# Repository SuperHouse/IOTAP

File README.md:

IoT WiFi Access Point
=====================

Simple WiFi devices typically don't support enterprise level WiFi
authentication, which means they all share a single password. If
an IoT device is compromised, the password can be exposed and changing
the password on many devices is painful.

This project aims to create a WiFi access point that supports
personal pre-shared keys (PPSK) so that each device can be given its
own password. Access privileges for any device can then be revoked
without requiring changes to any other device.

More information is available at:

  https://www.superhouse.tv/iotap

Hardware
--------
The "Hardware" directory contains the PCB design as an EAGLE project.

Enclosure
---------
The enclosure is model AK-NW-40 from SZOMK:

  https://www.aliexpress.com/item/33043522751.html

Credits
-------
 * Jonathan Oxer <jon@oxer.com.au>
 * Tony Smith
 * Austin's Creations <https://www.austinscreations.ca/>
 * All the folks watching and commenting on the streams!

License
-------
Copyright 2020-2022 SuperHouse Automation Pty Ltd  www.superhouse.tv  

The hardware portion of this project is licensed under the TAPR Open
Hardware License (www.tapr.org/OHL). The "license" folder within this
repository contains a copy of this license in plain text format.

The software portion of this project is licensed under the Simplified
BSD License. The "licence" folder within this project contains a
copy of this license in plain text format.

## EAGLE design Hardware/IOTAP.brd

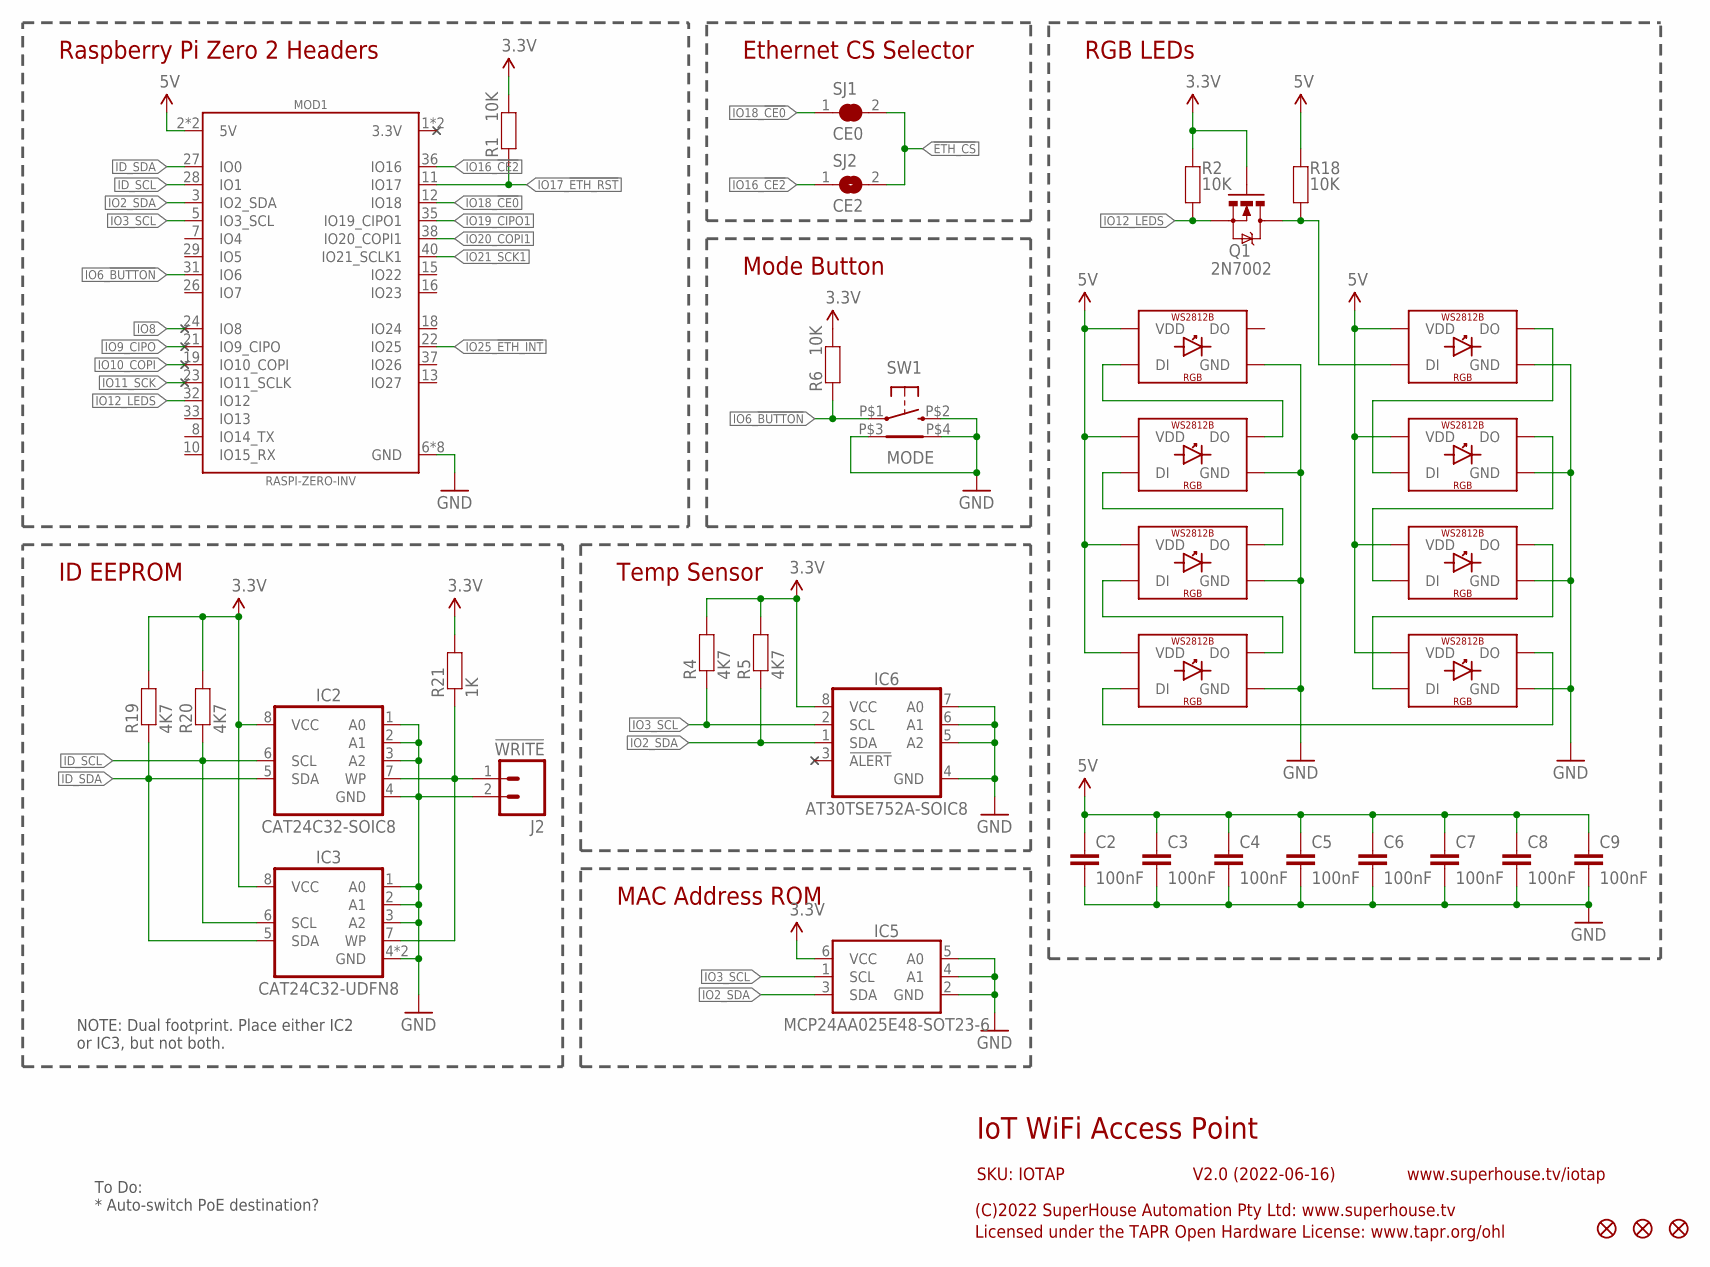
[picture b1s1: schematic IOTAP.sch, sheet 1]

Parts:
C2, C3, C4, C5, C6, C7, C8, C9: 100nF; C0603
FID1, FID2, FID3: FIDUCIAL1X2.5; FIDUCIAL-1X2.5
IC2: CAT24C32-SOIC8; SOIC8
IC3: CAT24C32-UDFN8; UDFN8
IC5: MCP24AA025E48-SOT23-6; SOT23-6
IC6: AT30TSE752A-SOIC8; SOIC8
J2: !WRITE; 1X02
LED1, LED2, LED3, LED4, LED5, LED6, LED7, LED8: WS2812B5050; WS2812B
MOD1: RASPI-ZERO-INV; RPI-ZERO-INV
Q1: 2N7002; SOT23-3
R1, R2, R6, R18: 10K; R0603
R4, R5, R19, R20: 4K7; R0603
R21: 1K; R0603
SJ1: CE0; SJC
SJ2: CE2; SJ
SW1: MODE; TC-120V

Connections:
3.3V: IC2.8 (VCC), IC3.8 (VCC), IC5.6 (VCC), IC6.8 (VCC), Q1.1 (G), R1.2, R2.2, R4.2, R5.2, R6.2, R19.2, R20.2, R21.2; also elsewhere on the board
5V: C2.1, C3.1, C4.1, C5.1, C6.1, C7.1, C8.1, C9.1, LED1.1-VDD (VDD), LED2.1-VDD (VDD), LED3.1-VDD (VDD), LED4.1-VDD (VDD), LED5.1-VDD (VDD), LED6.1-VDD (VDD), LED7.1-VDD (VDD), LED8.1-VDD (VDD), MOD1.2 (5V), MOD1.4 (5V), R18.2; also elsewhere on the board
!ETH_CS: SJ1.2, SJ2.2; also elsewhere on the board
GND: C2.2, C3.2, C4.2, C5.2, C6.2, C7.2, C8.2, C9.2, IC2.1 (A0), IC2.2 (A1), IC2.3 (A2), IC2.4 (GND), IC3.1 (A0), IC3.2 (A1), IC3.3 (A2), IC3.4 (GND), IC3.PAD (GND), IC5.2 (GND), IC5.4 (A1), IC5.5 (A0), IC6.4 (GND), IC6.5 (A2), IC6.6 (A1), IC6.7 (A0), J2.2, LED1.3-GND (GND), LED2.3-GND (GND), LED3.3-GND (GND), LED4.3-GND (GND), LED5.3-GND (GND), LED6.3-GND (GND), LED7.3-GND (GND), LED8.3-GND (GND), MOD1.6 (GND), MOD1.9 (GND), MOD1.14 (GND), MOD1.20 (GND), MOD1.25 (GND), MOD1.30 (GND), MOD1.34 (GND), MOD1.39 (GND), SW1.P$2 (2), SW1.P$3 (TAB1), SW1.P$4 (TAB2); also elsewhere on the board
ID_SCL: IC2.6 (SCL), IC3.6 (SCL), MOD1.28 (IO1), R20.1
ID_SDA: IC2.5 (SDA), IC3.5 (SDA), MOD1.27 (IO0), R19.1
IO2_SDA: IC5.3 (SDA), IC6.1 (SDA), MOD1.3 (IO2_SDA), R5.1; also elsewhere on the board
IO3_SCL: IC5.1 (SCL), IC6.2 (SCL), MOD1.5 (IO3_SCL), R4.1; also elsewhere on the board
IO6_!BUTTON: MOD1.31 (IO6), R6.1, SW1.P$1 (1)
IO8: MOD1.24 (IO8)
IO9_CIPO: MOD1.21 (IO9_CIPO)
IO10_COPI: MOD1.19 (IO10_COPI)
IO11_SCK: MOD1.23 (IO11_SCLK)
IO12_LEDS: MOD1.32 (IO12), Q1.2 (S), R2.1
IO16_!CE2: MOD1.36 (IO16), SJ2.1
IO17_!ETH_RST: MOD1.11 (IO17), R1.1; also elsewhere on the board
IO18_!CE0: MOD1.12 (IO18), SJ1.1
IO19_CIPO1: MOD1.35 (IO19_CIPO1); also elsewhere on the board
IO20_COPI1: MOD1.38 (IO20_COPI1); also elsewhere on the board
IO21_SCK1: MOD1.40 (IO21_SCLK1); also elsewhere on the board
IO25_!ETH_INT: MOD1.22 (IO25); also elsewhere on the board
LEDS: LED1.4-DIN (DI), Q1.3 (D), R18.1
unnamed: IC2.7 (WP), IC3.7 (WP), J2.1, R21.1
unnamed: LED4.2-DOUT (DO), LED5.4-DIN (DI)
unnamed: LED5.2-DOUT (DO), LED6.4-DIN (DI)
unnamed: LED6.2-DOUT (DO), LED7.4-DIN (DI)
unnamed: LED7.2-DOUT (DO), LED8.4-DIN (DI)
unnamed: LED1.2-DOUT (DO), LED2.4-DIN (DI)
unnamed: LED2.2-DOUT (DO), LED3.4-DIN (DI)
unnamed: LED3.2-DOUT (DO), LED4.4-DIN (DI)

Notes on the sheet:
IoT WiFi Access Point
V2.0 (2022-06-16)
SKU: IOTAP
(C)2022 SuperHouse Automation Pty Ltd: www.superhouse.tv
Licensed under the TAPR Open Hardware License: www.tapr.org/ohl
www.superhouse.tv/iotap
RGB LEDs
Raspberry Pi Zero 2 Headers
To Do: * Auto-switch PoE destination?
Mode Button
Temp Sensor
Ethernet CS Selector
ID EEPROM
NOTE: Dual footprint. Place either IC2 or IC3, but not both.
MAC Address ROM

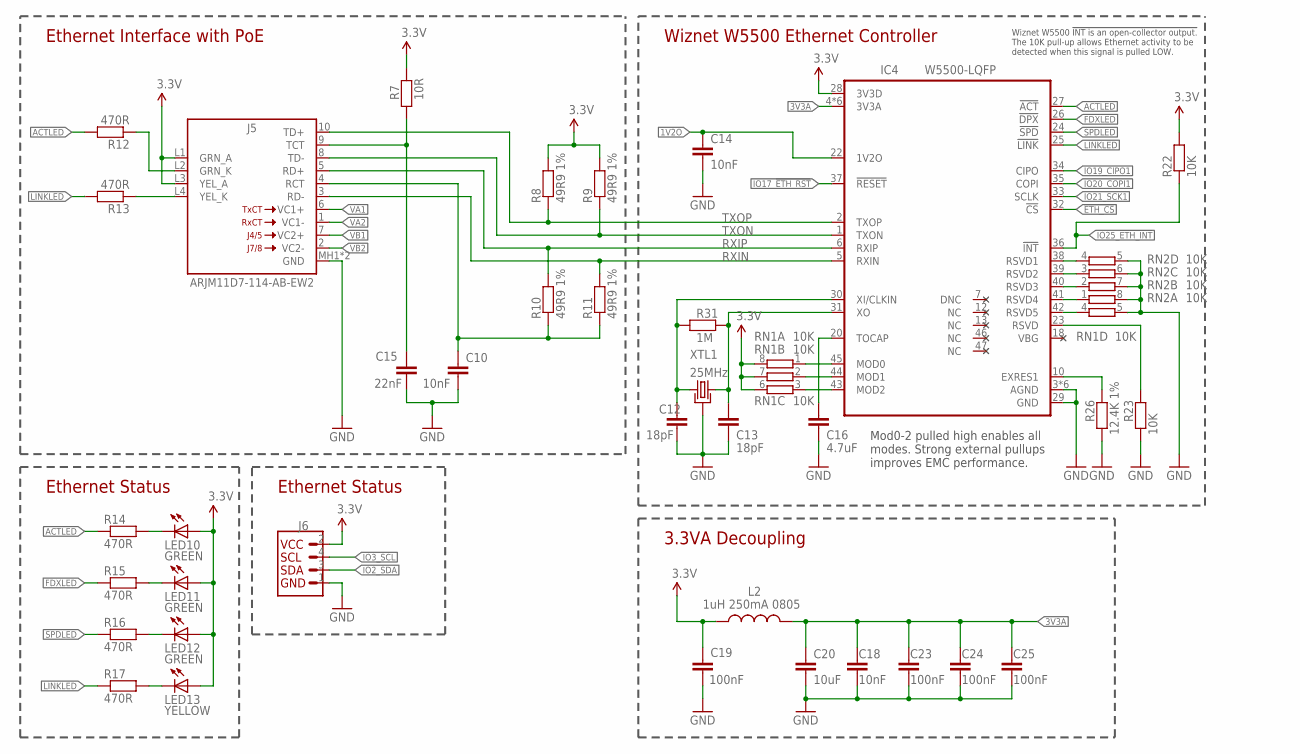
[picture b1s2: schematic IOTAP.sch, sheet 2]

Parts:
C10, C14, C18: 10nF; C0603
C12, C13: 18pF; C0603
C15: 22nF; C0603
C16: 4.7uF; C0603
C19, C23, C24, C25: 100nF; C0603
C20: 10uF; C0805
IC4: W5500-LQFP; LQFP48
J5: ARJM11D7-114-AB-EW2; ARJM11D7114ABEW2
J6: QWIICJS-1MM; 1X04_QWIIC_1MM_RA
L2: 1uH 250mA 0805; L2012C
LED10, LED11, LED12: GREEN; LED-0603
LED13: YELLOW; LED-0603
R7: 10R; R0603
R8, R9, R10, R11: 49R9 1%; R0603
R12, R13, R14, R15, R16, R17: 470R; R0603
R22, R23: 10K; R0603
R26: 12.4K 1%; R0603
R31: 1M; R0603
RN1, RN2: 10K; CAY16
XTL1: 25MHz; CRYSTAL-SMD-3X2

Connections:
1V2O: C14.1, IC4.22 (1V2O)
3.3V: C19.1, IC4.28 (3V3D), J5.L1 (GRN_A), J5.L3 (YEL_A), J6.2, L2.1, LED10.A, LED11.A, LED12.A, LED13.A, R7.1, R8.2, R9.2, R22.2, RN1.6 (2), RN1.7 (2), RN1.8 (2); also elsewhere on the board
3V3A: C18.1, C20.1, C23.1, C24.1, C25.1, IC4.4 (3V3A), IC4.8 (3V3A), IC4.11 (3V3A), IC4.15 (3V3A), IC4.17 (3V3A), IC4.21 (3V3A), L2.2
!ETH_CS: IC4.32 (!CS); also elsewhere on the board
ACTLED: IC4.27 (!ACT), R12.2, R14.1
FDXLED: IC4.26 (!DPX), R15.1
GND: C10.2, C12.2, C13.2, C14.2, C15.2, C16.2, C18.2, C19.2, C20.2, C23.2, C24.2, C25.2, IC4.3 (AGND), IC4.9 (AGND), IC4.14 (AGND), IC4.16 (AGND), IC4.19 (AGND), IC4.29 (GND), IC4.48 (AGND), J5.MH1 (GND), J5.MH2 (GND), J6.1, R23.2, R26.2, RN1.5 (2), RN2.5 (2), RN2.6 (2), RN2.7 (2), RN2.8 (2), XTL1.2 (GND), XTL1.4 (GND); also elsewhere on the board
IO2_SDA: J6.3; also elsewhere on the board
IO3_SCL: J6.4; also elsewhere on the board
IO17_!ETH_RST: IC4.37 (!RESET); also elsewhere on the board
IO19_CIPO1: IC4.34 (CIPO); also elsewhere on the board
IO20_COPI1: IC4.35 (COPI); also elsewhere on the board
IO21_SCK1: IC4.33 (SCLK); also elsewhere on the board
IO25_!ETH_INT: IC4.36 (!INT), R22.1; also elsewhere on the board
LINKLED: IC4.25 (!LINK), R13.2, R17.1
unnamed: J5.L4 (YEL_K), R13.1
unnamed: J5.L2 (GRN_K), R12.1
unnamed: C13.1, IC4.31 (XO), R31.1, XTL1.3 (2)
unnamed: C10.1, J5.4 (RCT), R10.1, R11.1
unnamed: LED12.C, R16.2
unnamed: C12.1, IC4.30 (XI/CLKIN), R31.2, XTL1.1
unnamed: LED13.C, R17.2
unnamed: C16.1, IC4.20 (TOCAP)
unnamed: C15.1, J5.9 (TCT), R7.2
unnamed: IC4.10 (EXRES1), R26.1
unnamed: IC4.23 (RSVD), R23.1
unnamed: IC4.45 (MOD0), RN1.1
unnamed: IC4.44 (MOD1), RN1.2 (1)
unnamed: IC4.43 (MOD2), RN1.3 (1)
unnamed: IC4.42 (RSVD5), RN1.4 (1)
unnamed: IC4.41 (RSVD4), RN2.1
unnamed: IC4.40 (RSVD3), RN2.2 (1)
unnamed: IC4.39 (RSVD2), RN2.3 (1)
unnamed: IC4.38 (RSVD1), RN2.4 (1)
unnamed: LED11.C, R15.2
unnamed: LED10.C, R14.2
RXIN: IC4.5 (RXIN), J5.3 (RD-), R11.2
RXIP: IC4.6 (RXIP), J5.5 (RD+), R10.2
SPDLED: IC4.24 (!SPD), R16.1
TXON: IC4.1 (TXON), J5.8 (TD-), R9.1
TXOP: IC4.2 (TXOP), J5.10 (TD+), R8.1
VA1: J5.6 (VC1+); also elsewhere on the board
VA2: J5.1 (VC1-); also elsewhere on the board
VB1: J5.7 (VC2+); also elsewhere on the board
VB2: J5.2 (VC2-); also elsewhere on the board

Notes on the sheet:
Ethernet Status
Ethernet Interface with PoE
Wiznet W5500 Ethernet Controller
Mod0-2 pulled high enables all modes. Strong external pullups improves EMC performance.
Wiznet W5500 !INT is an open-collector output. The 10K pull-up allows Ethernet activity to be detected when this signal is pulled LOW.
3.3VA Decoupling

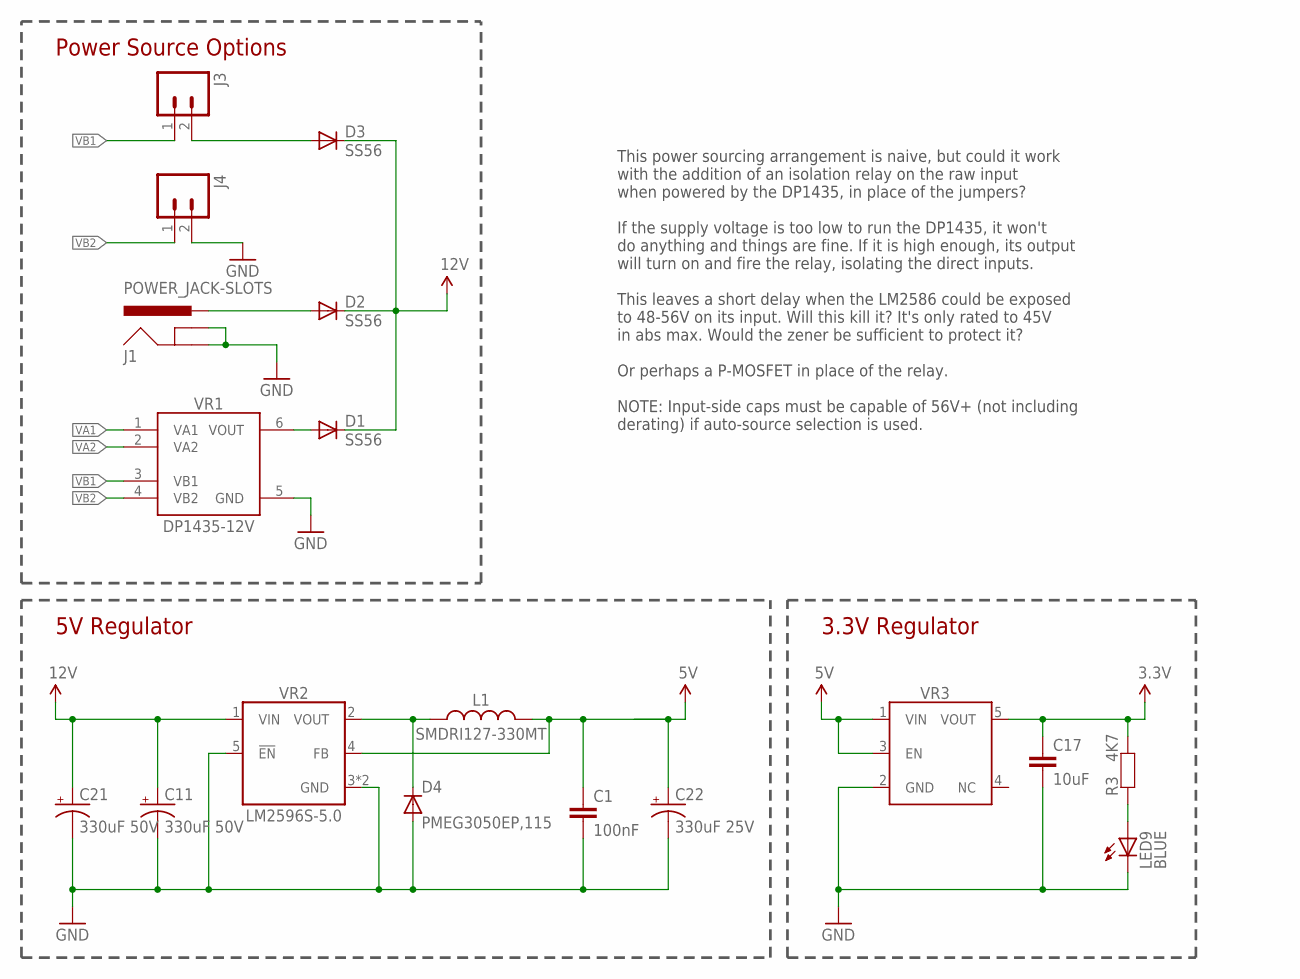
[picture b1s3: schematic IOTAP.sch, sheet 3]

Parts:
C1: 100nF; C0603
C11, C21: 330uF 50V; PANASONIC_G
C17: 10uF; C0805
C22: 330uF 25V; PANASONIC_G
D1, D2, D3: SS56; SMA-DIODE
D4: PMEG3050EP,115; SOD-128
J1: POWER_JACK-SLOTS; POWER_JACK_SLOTS
J3, J4: M02-PIN-RA; 1X02-P-RA
L1: SMDRI127-330MT; INDPM120120X800N
LED9: BLUE; LED-0603
R3: 4K7; R0603
VR1: DP1435-12V; DP1435
VR2: LM2596S-5.0; TO170P1435X465-6N
VR3: AP2112KSOT25; SOT23-5

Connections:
3.3V: C17.1, R3.2, VR3.5 (VOUT); also elsewhere on the board
5V: C1.1, C22.+, L1.2, VR2.4 (FB), VR3.1 (VIN), VR3.3 (EN); also elsewhere on the board
12V: C11.+, C21.+, D1.C, D2.C, D3.C, VR2.1 (VIN)
GND: C1.2, C11.-, C17.2, C21.-, C22.-, D4.2 (A), J1.GND, J1.GNDBREAK, J4.2, LED9.C, VR1.5 (GND), VR2.3 (GND), VR2.5 (!EN), VR2.6 (GND), VR3.2 (GND); also elsewhere on the board
unnamed: D3.A, J3.2
unnamed: D4.1 (C), L1.1, VR2.2 (VOUT)
unnamed: LED9.A, R3.1
unnamed: D2.A, J1.PWR
unnamed: D1.A, VR1.6 (VOUT)
VA1: VR1.1 (VA1); also elsewhere on the board
VA2: VR1.2 (VA2); also elsewhere on the board
VB1: J3.1, VR1.3 (VB1); also elsewhere on the board
VB2: J4.1, VR1.4 (VB2); also elsewhere on the board

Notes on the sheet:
Power Source Options
This power sourcing arrangement is naive, but could it work with the addition of an isolation relay on the raw input when powered by the DP1435, in place of the jumpers? If the supply voltage is too low to run the DP1435, it won't do anything and things are fine. If it is high enough, its output wi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
5V Regulator
3.3V Regulator

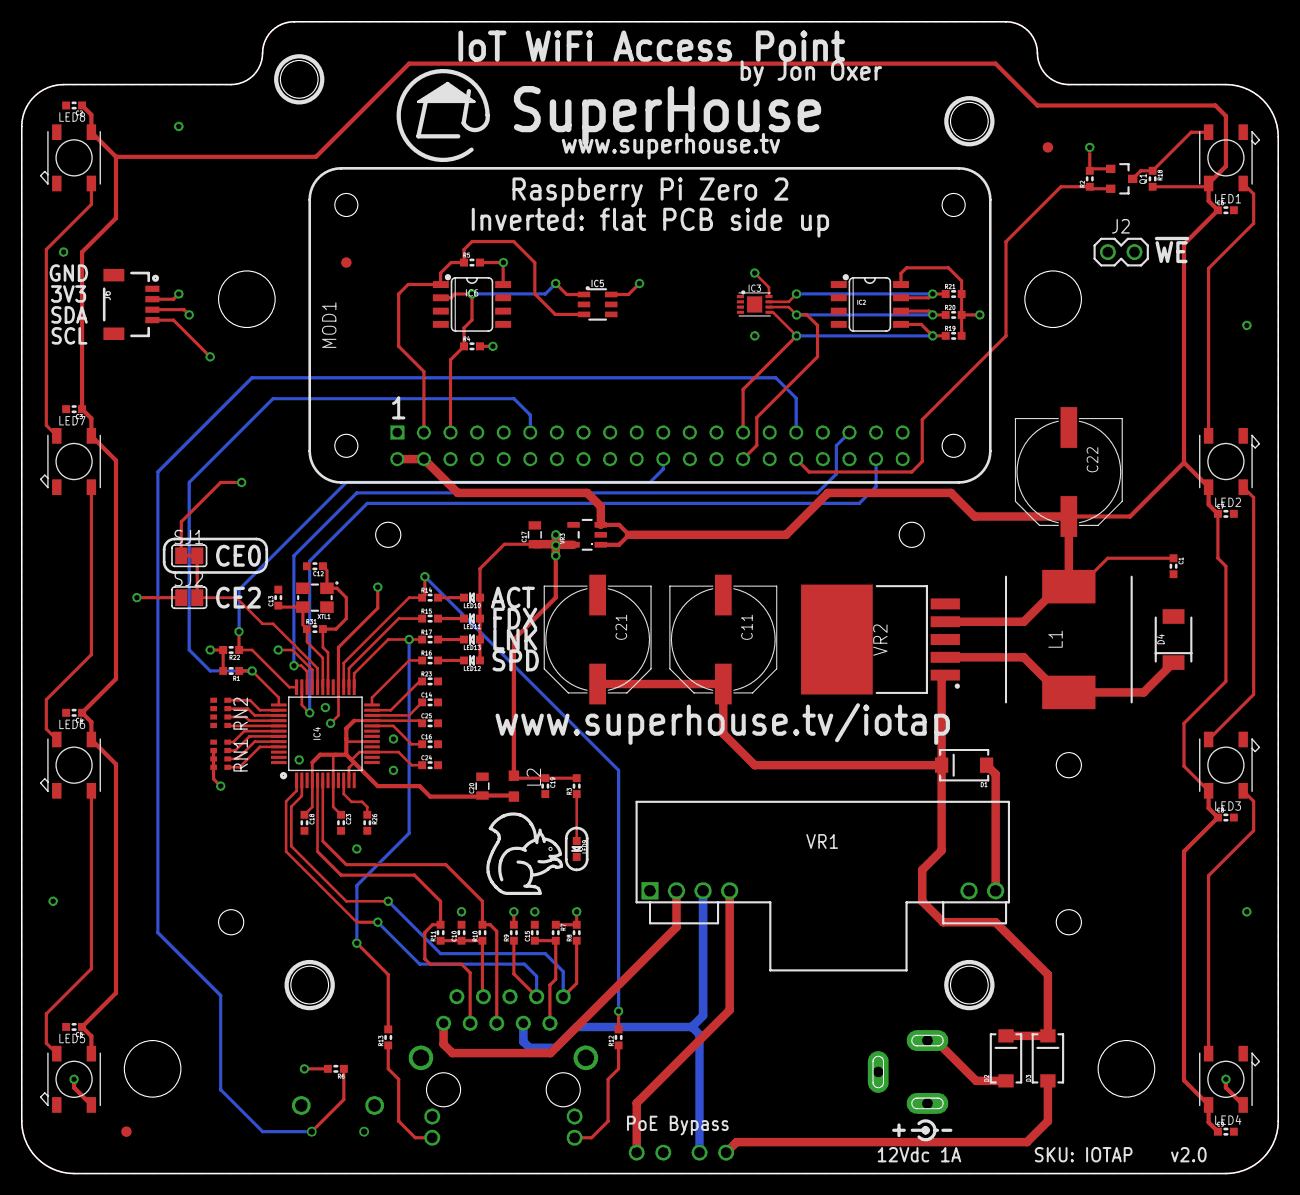
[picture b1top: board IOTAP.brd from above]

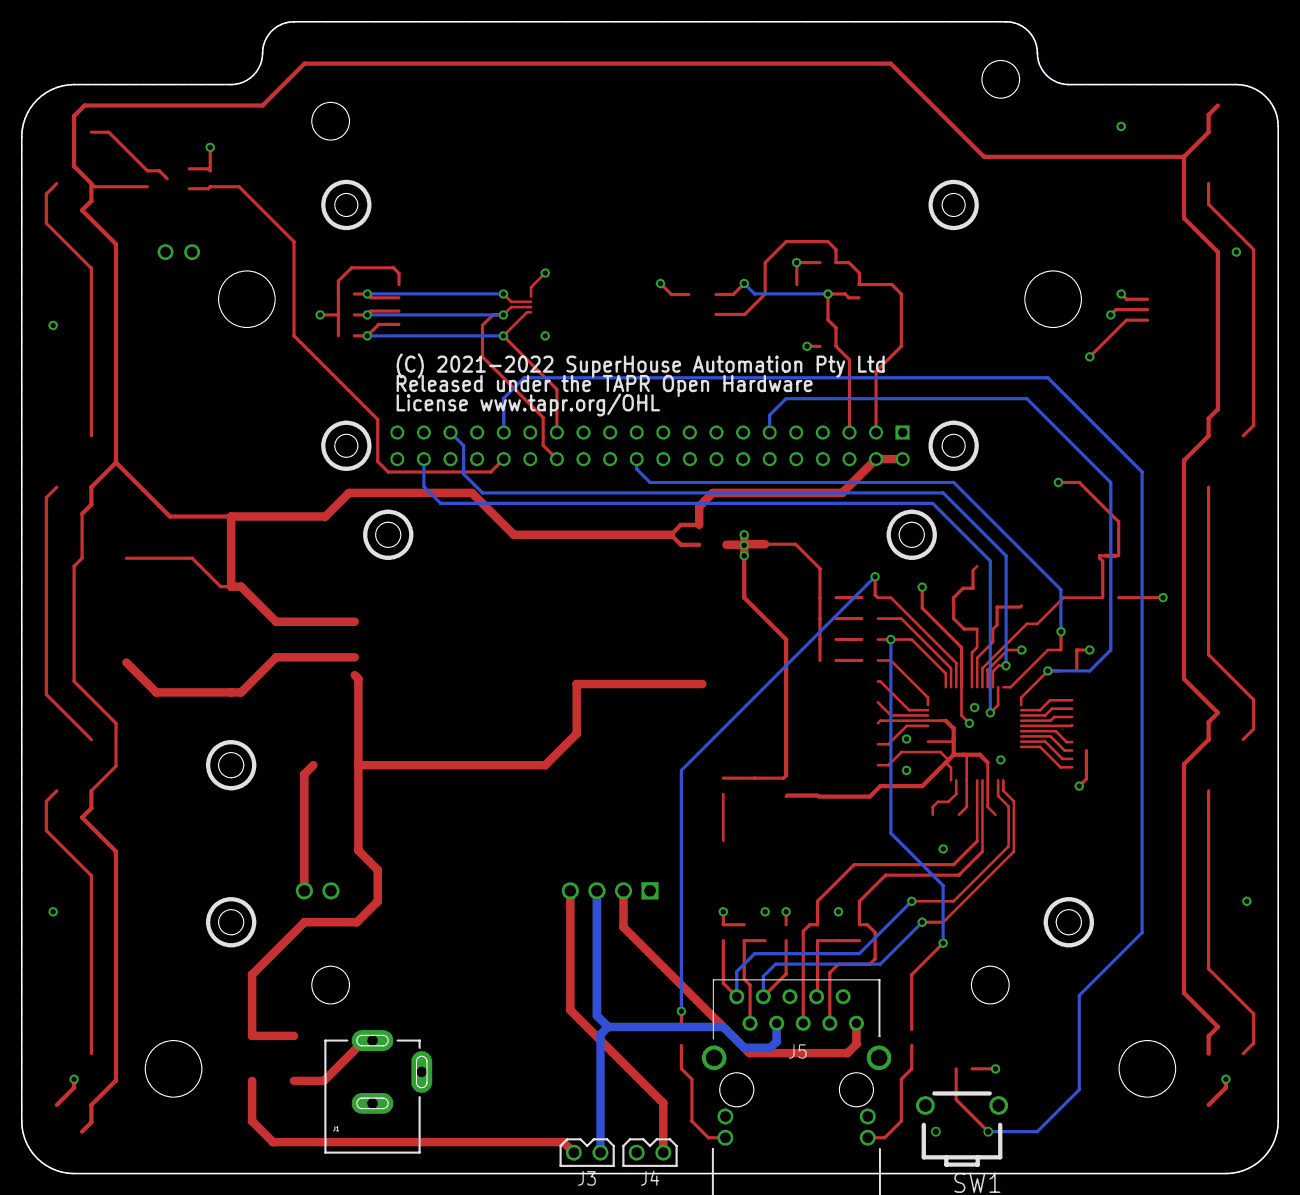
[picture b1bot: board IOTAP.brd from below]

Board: 4 copper layers, 120.0 x 110.0 mm, 94 parts (5 on the bottom side), 67 nets.

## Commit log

2021-09-28 Initial import.
2021-10-07 Fixed footprint for RJ45 socket.
2022-10-23 Major redesign based on Raspberry Pi Zero 2.
2022-10-23 Added image of board.
2022-10-23 Added license files.
2022-10-23 Added README.
2022-10-23 Removed obsolete references to old project.
2022-10-23 Added link to enclosure.
2022-11-20 Added first pass of config files and setup script for initial testing.
2022-11-26 Update iotap
    Added 20 second delay before adding interfaces to bridge device
2022-12-11 Added systemctl config to add Eth0 to the bridge device.
2022-12-11 Removed obsolete attempt to add Eth0 to bridge.
2022-12-11 Added servicectl call.
2022-12-11 Moved files into the correct place.
2022-12-11 Added contributors.
2022-12-11 Added Austin in credits.
2022-12-15 Removed sudo, sleep and brctl commands
2022-12-15 Use only channel 1, 6 or 11 in 2.4Ghz
    changed to channel 6 from 7
2022-12-15 Removed brctl command
2022-12-15 Removed line about bridge bug
2022-12-15 If you don't have w5500 installed, you can change W5500_installed to no

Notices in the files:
Hardware/IOTAP.brd:
(C) 2021-2022 SuperHouse Automation Pty Ltd
